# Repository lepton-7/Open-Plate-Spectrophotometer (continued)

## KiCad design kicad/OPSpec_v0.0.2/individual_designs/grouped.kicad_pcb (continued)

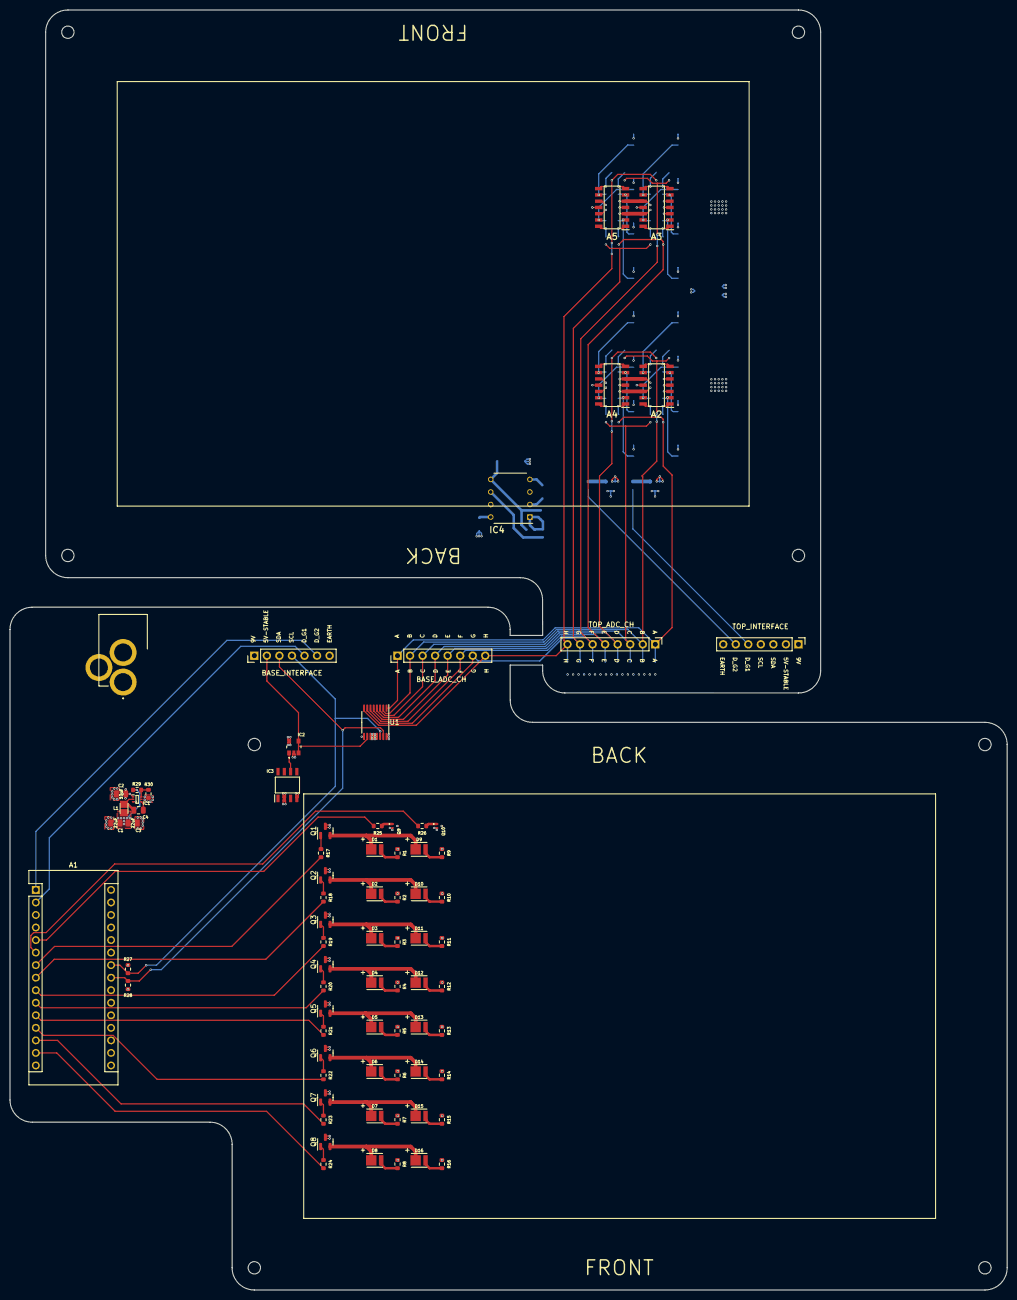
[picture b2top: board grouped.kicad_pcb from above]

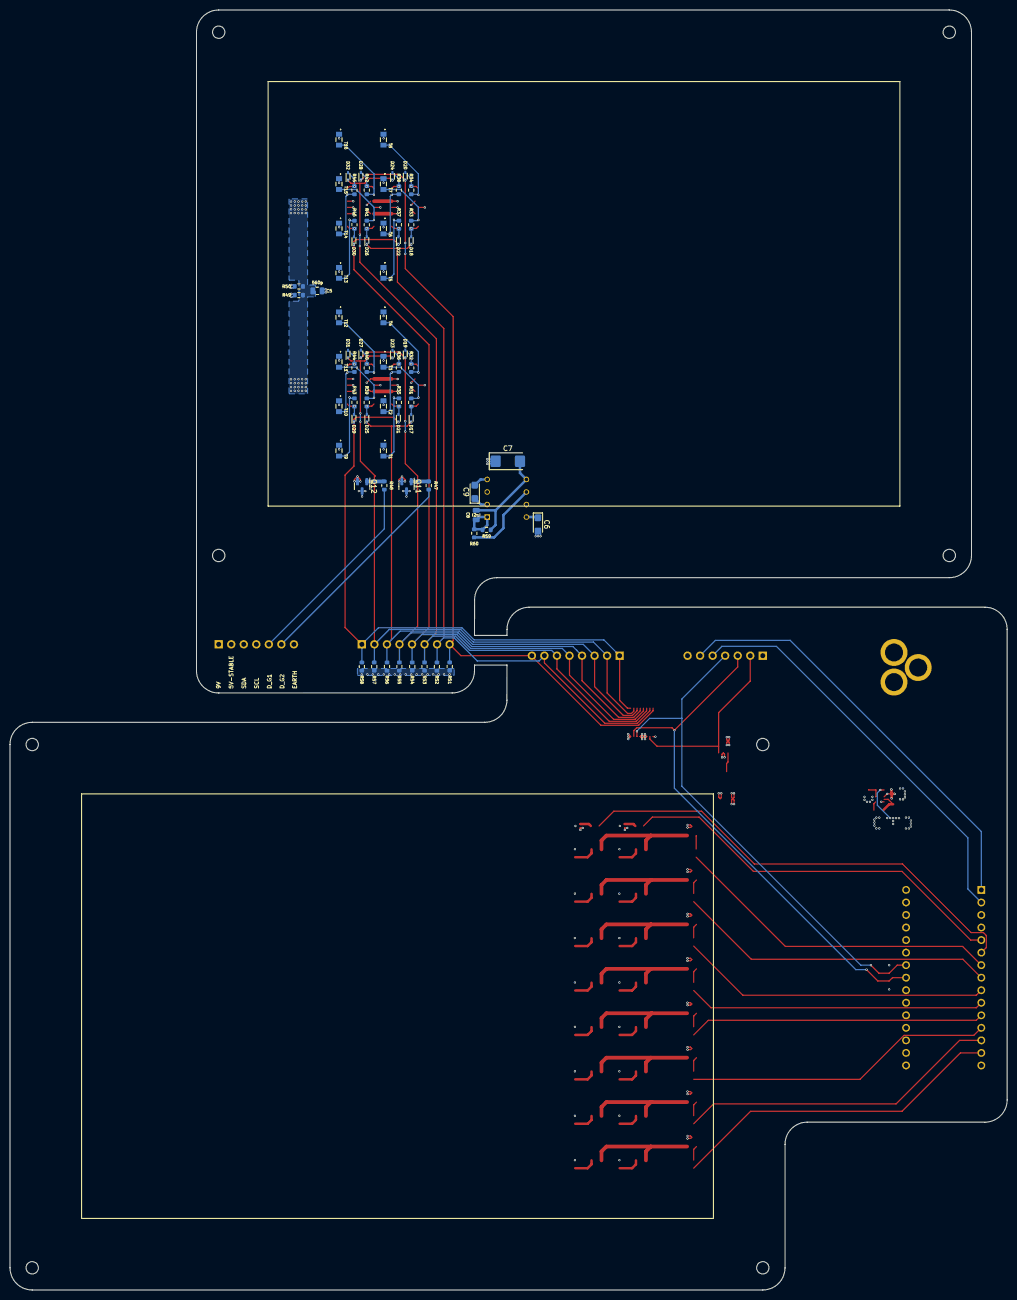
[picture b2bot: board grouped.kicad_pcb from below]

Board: 4 copper layers, 202.0 x 259.3 mm, 153 parts (73 on the bottom side), 112 nets.

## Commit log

2024-02-03 Prep cleanup
2024-02-03 Removed temp
2024-03-10 Test version grid description
2024-03-11 Test schematic description
2024-03-11 sub and sup script for github
2024-03-11 Fixed latex notation
2025-06-15 Split ADC and detector grid controls to own sources
2025-06-15 Communication with the IO expanders
2025-06-15 Populate detector grid operation funcs
2025-06-15 Routine kicad save update
2025-06-15 Led interafacing functions
